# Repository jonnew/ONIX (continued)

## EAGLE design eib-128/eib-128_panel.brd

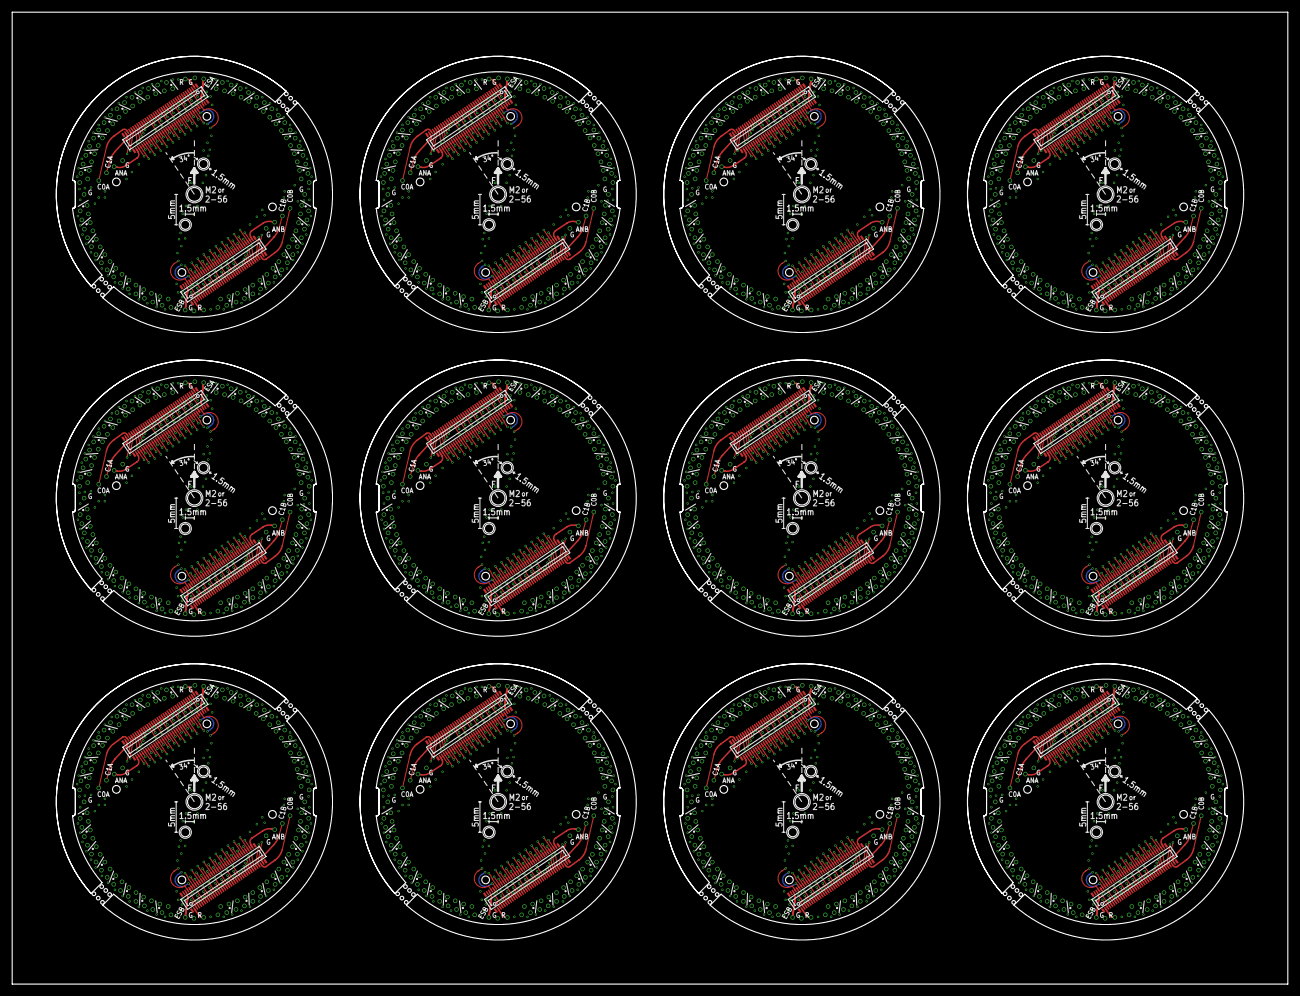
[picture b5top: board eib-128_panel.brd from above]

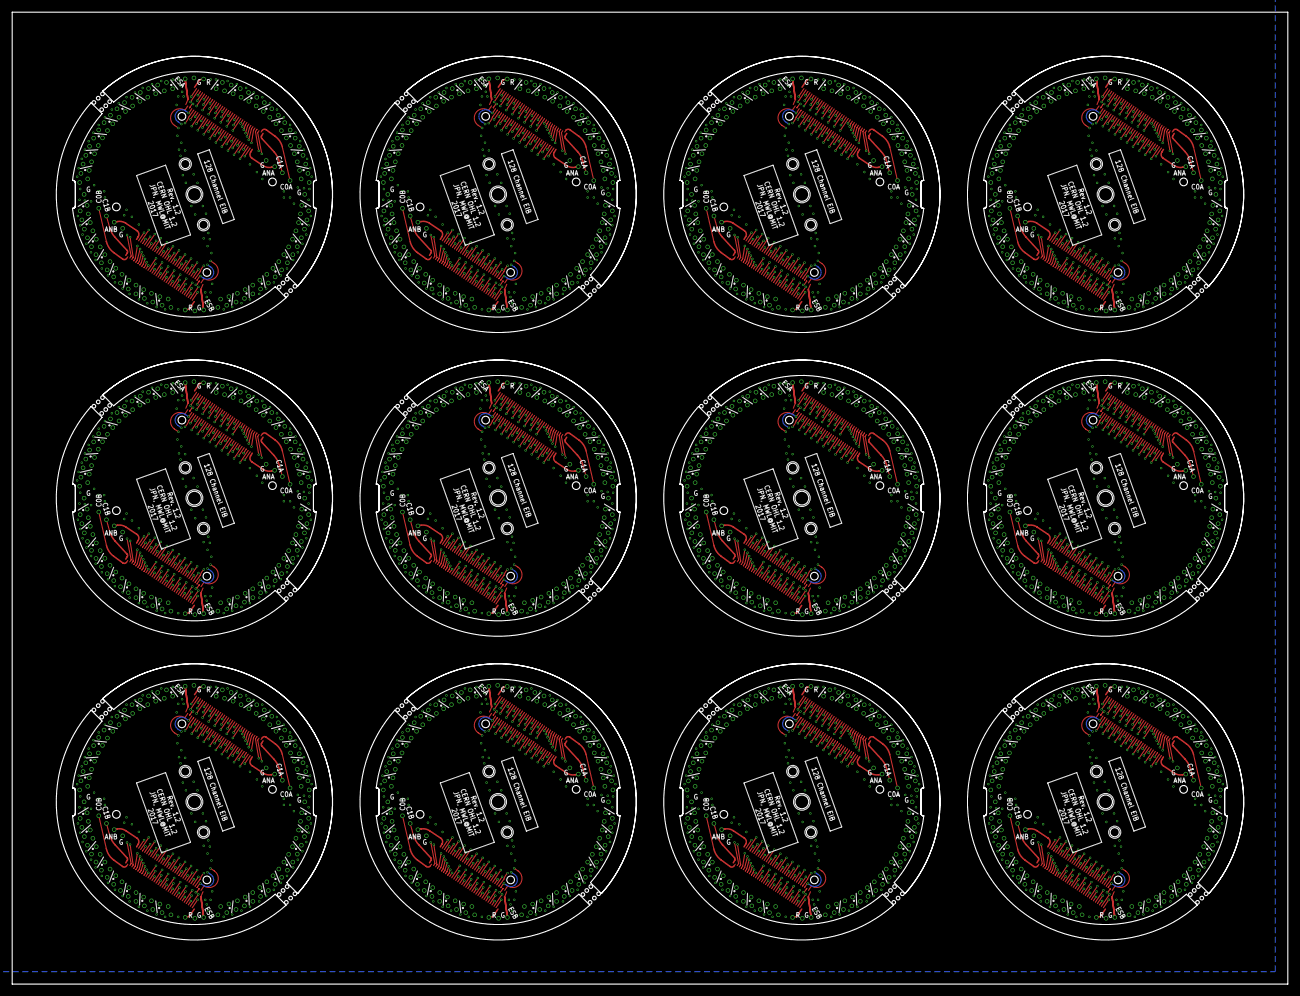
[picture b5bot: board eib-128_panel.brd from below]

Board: 4 copper layers, 210.0 x 160.0 mm, 612 parts (192 on the bottom side), 1657 nets.

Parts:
A, A1, A2, A3, A4, A5, A6, A7, A8, A9, A10, A11: DF40HEAD; DF40-70HEAD
AN_A, AN_A1, AN_A2, AN_A3, AN_A4, AN_A5, AN_A6, AN_A7, AN_A8, AN_A9, AN_A10, AN_A11: LRG_GP; GOLDPIN_0.5ID_0.7OD
AN_B, AN_B1, AN_B2, AN_B3, AN_B4, AN_B5, AN_B6, AN_B7, AN_B8, AN_B9, AN_B10, AN_B11: LRG_GP; GOLDPIN_0.5ID_0.7OD
B, B1, B2, B3, B4, B5, B6, B7, B8, B9, B10, B11: DF40HEAD; DF40-70HEAD
CAT0_A, CAT0_A1, CAT0_A2, CAT0_A3, CAT0_A4, CAT0_A5, CAT0_A6, CAT0_A7, CAT0_A8, CAT0_A9, CAT0_A10, CAT0_A11, CAT0_B, CAT0_B1, CAT0_B2, CAT0_B3, CAT0_B4, CAT0_B5, CAT0_B6, CAT0_B7, CAT0_B8, CAT0_B9, CAT0_B10, CAT0_B11, CAT1_A, CAT1_A1, CAT1_A2, CAT1_A3, CAT1_A4, CAT1_A5, CAT1_A6, CAT1_A7, CAT1_A8, CAT1_A9, CAT1_A10, CAT1_A11, CAT1_B, CAT1_B1, CAT1_B2, CAT1_B3, CAT1_B4, CAT1_B5, CAT1_B6, CAT1_B7, CAT1_B8, CAT1_B9, CAT1_B10, CAT1_B11: LRG_GP; GOLDPIN_0.5ID_0.7OD
ESTIM_A, ESTIM_A1, ESTIM_A2, ESTIM_A3, ESTIM_A4, ESTIM_A5, ESTIM_A6, ESTIM_A7, ESTIM_A8, ESTIM_A9, ESTIM_A10, ESTIM_A11: LRG_GP; GOLDPIN_0.5ID_0.7OD
ESTIM_B, ESTIM_B1, ESTIM_B2, ESTIM_B3, ESTIM_B4, ESTIM_B5, ESTIM_B6, ESTIM_B7, ESTIM_B8, ESTIM_B9, ESTIM_B10, ESTIM_B11: LRG_GP; GOLDPIN_0.5ID_0.7OD
GND0, GND1, GND2, GND3, GND4, GND5, GND6, GND7, GND8, GND9, GND10, GND11, GND12, GND13, GND14, GND15, GND16, GND17, GND18, GND19, GND20, GND21, GND22, GND23, GND24, GND25, GND26, GND27, GND28, GND29, GND30, GND31, GND32, GND33, GND34, GND35, GND36, GND37, GND38, GND39, GND40, GND41, GND42, GND43, GND44, GND45, GND46, GND47: LRG_GP; GOLDPIN_0.5ID_0.7OD
REF_A0, REF_A1, REF_A2, REF_A3, REF_A4, REF_A5, REF_A6, REF_A7, REF_A8, REF_A9, REF_A10, REF_A11: LRG_GP; GOLDPIN_0.5ID_0.7OD
REF_B0, REF_B1, REF_B2, REF_B3, REF_B4, REF_B5, REF_B6, REF_B7, REF_B8, REF_B9, REF_B10, REF_B11: LRG_GP; GOLDPIN_0.5ID_0.7OD
SHLD_A, SHLD_A1, SHLD_A2, SHLD_A3, SHLD_A4, SHLD_A5, SHLD_A6, SHLD_A7, SHLD_A8, SHLD_A9, SHLD_A10, SHLD_A11: LRG_GP; GOLDPIN_0.5ID_0.7OD
SHLD_B, SHLD_B1, SHLD_B2, SHLD_B3, SHLD_B4, SHLD_B5, SHLD_B6, SHLD_B7, SHLD_B8, SHLD_B9, SHLD_B10, SHLD_B11: LRG_GP; GOLDPIN_0.5ID_0.7OD
TET0, TET32, TET64, TET96, TET128, TET160, TET192, TET224, TET256, TET288, TET320, TET352: 0; TETRODE_128_0.5ID_0.7OD
TET1, TET33, TET65, TET97, TET129, TET161, TET193, TET225, TET257, TET289, TET321, TET353: 1; TETRODE_128_0.5ID_0.7OD
TET2, TET34, TET66, TET98, TET130, TET162, TET194, TET226, TET258, TET290, TET322, TET354: 2; TETRODE_128_0.5ID_0.7OD
TET3, TET35, TET67, TET99, TET131, TET163, TET195, TET227, TET259, TET291, TET323, TET355: 3; TETRODE_128_0.5ID_0.7OD
TET4, TET36, TET68, TET100, TET132, TET164, TET196, TET228, TET260, TET292, TET324, TET356: 4; TETRODE_128_0.5ID_0.7OD
TET5, TET37, TET69, TET101, TET133, TET165, TET197, TET229, TET261, TET293, TET325, TET357: 5; TETRODE_128_0.5ID_0.7OD
TET6, TET38, TET70, TET102, TET134, TET166, TET198, TET230, TET262, TET294, TET326, TET358: 6; TETRODE_128_0.5ID_0.7OD
TET7, TET39, TET71, TET103, TET135, TET167, TET199, TET231, TET263, TET295, TET327, TET359: 7; TETRODE_128_0.5ID_0.7OD
TET8, TET40, TET72, TET104, TET136, TET168, TET200, TET232, TET264, TET296, TET328, TET360: 8; TETRODE_128_0.5ID_0.7OD
TET9, TET41, TET73, TET105, TET137, TET169, TET201, TET233, TET265, TET297, TET329, TET361: 9; TETRODE_128_0.5ID_0.7OD
TET10, TET42, TET74, TET106, TET138, TET170, TET202, TET234, TET266, TET298, TET330, TET362: 10; TETRODE_128_0.5ID_0.7OD
TET11, TET43, TET75, TET107, TET139, TET171, TET203, TET235, TET267, TET299, TET331, TET363: 11; TETRODE_128_0.5ID_0.7OD
TET12, TET44, TET76, TET108, TET140, TET172, TET204, TET236, TET268, TET300, TET332, TET364: 12; TETRODE_128_0.5ID_0.7OD
TET13, TET45, TET77, TET109, TET141, TET173, TET205, TET237, TET269, TET301, TET333, TET365: 13; TETRODE_128_0.5ID_0.7OD
TET14, TET46, TET78, TET110, TET142, TET174, TET206, TET238, TET270, TET302, TET334, TET366: 14; TETRODE_128_0.5ID_0.7OD
TET15, TET47, TET79, TET111, TET143, TET175, TET207, TET239, TET271, TET303, TET335, TET367: 15; TETRODE_128_0.5ID_0.7OD
TET16, TET48, TET80, TET112, TET144, TET176, TET208, TET240, TET272, TET304, TET336, TET368: 16; TETRODE_128_0.5ID_0.7OD
TET17, TET49, TET81, TET113, TET145, TET177, TET209, TET241, TET273, TET305, TET337, TET369: 17; TETRODE_128_0.5ID_0.7OD
TET18, TET50, TET82, TET114, TET146, TET178, TET210, TET242, TET274, TET306, TET338, TET370: 18; TETRODE_128_0.5ID_0.7OD
TET19, TET51, TET83, TET115, TET147, TET179, TET211, TET243, TET275, TET307, TET339, TET371: 19; TETRODE_128_0.5ID_0.7OD
TET20, TET52, TET84, TET116, TET148, TET180, TET212, TET244, TET276, TET308, TET340, TET372: 20; TETRODE_128_0.5ID_0.7OD
TET21, TET53, TET85, TET117, TET149, TET181, TET213, TET245, TET277, TET309, TET341, TET373: 21; TETRODE_128_0.5ID_0.7OD
TET22, TET54, TET86, TET118, TET150, TET182, TET214, TET246, TET278, TET310, TET342, TET374: 22; TETRODE_128_0.5ID_0.7OD
TET23, TET55, TET87, TET119, TET151, TET183, TET215, TET247, TET279, TET311, TET343, TET375: 23; TETRODE_128_0.5ID_0.7OD
TET24, TET56, TET88, TET120, TET152, TET184, TET216, TET248, TET280, TET312, TET344, TET376: 24; TETRODE_128_0.5ID_0.7OD
TET25, TET57, TET89, TET121, TET153, TET185, TET217, TET249, TET281, TET313, TET345, TET377: 25; TETRODE_128_0.5ID_0.7OD
TET26, TET58, TET90, TET122, TET154, TET186, TET218, TET250, TET282, TET314, TET346, TET378: 26; TETRODE_128_0.5ID_0.7OD
TET27, TET59, TET91, TET123, TET155, TET187, TET219, TET251, TET283, TET315, TET347, TET379: 27; TETRODE_128_0.5ID_0.7OD
TET28, TET60, TET92, TET124, TET156, TET188, TET220, TET252, TET284, TET316, TET348, TET380: 28; TETRODE_128_0.5ID_0.7OD
TET29, TET61, TET93, TET125, TET157, TET189, TET221, TET253, TET285, TET317, TET349, TET381: 29; TETRODE_128_0.5ID_0.7OD
TET30, TET62, TET94, TET126, TET158, TET190, TET222, TET254, TET286, TET318, TET350, TET382: 30; TETRODE_128_0.5ID_0.7OD
TET31, TET63, TET95, TET127, TET159, TET191, TET223, TET255, TET287, TET319, TET351, TET383: 31; TETRODE_128_0.5ID_0.7OD
U$1, U$2, U$3, U$4, U$5, U$6, U$7, U$8, U$9, U$10, U$11, U$12: EIB_MOUNT_A

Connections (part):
AN_A: A.36, AN_A.P$1
AN_A1: A1.36, AN_A1.P$1
AN_A2: A2.36, AN_A2.P$1
AN_A3: A3.36, AN_A3.P$1
AN_A4: A4.36, AN_A4.P$1
AN_A5: A5.36, AN_A5.P$1
AN_A6: A6.36, AN_A6.P$1
AN_A7: A7.36, AN_A7.P$1
AN_A8: A8.36, AN_A8.P$1
AN_A9: A9.36, AN_A9.P$1
AN_A10: A10.36, AN_A10.P$1
AN_A11: A11.36, AN_A11.P$1
AN_B: AN_B.P$1, B.36
AN_B1: AN_B1.P$1, B1.36
AN_B2: AN_B2.P$1, B2.36
AN_B3: AN_B3.P$1, B3.36
AN_B4: AN_B4.P$1, B4.36
AN_B5: AN_B5.P$1, B5.36
AN_B6: AN_B6.P$1, B6.36
AN_B7: AN_B7.P$1, B7.36
AN_B8: AN_B8.P$1, B8.36
AN_B9: AN_B9.P$1, B9.36
AN_B10: AN_B10.P$1, B10.36
AN_B11: AN_B11.P$1, B11.36
CAT0_A: A.34, CAT0_A.P$1
CAT0_A1: A1.34, CAT0_A1.P$1
CAT0_A2: A2.34, CAT0_A2.P$1
CAT0_A3: A3.34, CAT0_A3.P$1
CAT0_A4: A4.34, CAT0_A4.P$1
CAT0_A5: A5.34, CAT0_A5.P$1
CAT0_A6: A6.34, CAT0_A6.P$1
CAT0_A7: A7.34, CAT0_A7.P$1
CAT0_A8: A8.34, CAT0_A8.P$1
CAT0_A9: A9.34, CAT0_A9.P$1
CAT0_A10: A10.34, CAT0_A10.P$1
CAT0_A11: A11.34, CAT0_A11.P$1
CAT0_B: B.34, CAT0_B.P$1
CAT0_B1: B1.34, CAT0_B1.P$1
CAT0_B2: B2.34, CAT0_B2.P$1
CAT0_B3: B3.34, CAT0_B3.P$1
CAT0_B4: B4.34, CAT0_B4.P$1
CAT0_B5: B5.34, CAT0_B5.P$1
CAT0_B6: B6.34, CAT0_B6.P$1
CAT0_B7: B7.34, CAT0_B7.P$1
CAT0_B8: B8.34, CAT0_B8.P$1
CAT0_B9: B9.34, CAT0_B9.P$1
CAT0_B10: B10.34, CAT0_B10.P$1
CAT0_B11: B11.34, CAT0_B11.P$1
CAT1_A: A.35, CAT1_A.P$1
CAT1_A1: A1.35, CAT1_A1.P$1
CAT1_A2: A2.35, CAT1_A2.P$1
CAT1_A3: A3.35, CAT1_A3.P$1
CAT1_A4: A4.35, CAT1_A4.P$1
CAT1_A5: A5.35, CAT1_A5.P$1
CAT1_A6: A6.35, CAT1_A6.P$1
CAT1_A7: A7.35, CAT1_A7.P$1
CAT1_A8: A8.35, CAT1_A8.P$1
CAT1_A9: A9.35, CAT1_A9.P$1
CAT1_A10: A10.35, CAT1_A10.P$1
CAT1_A11: A11.35, CAT1_A11.P$1
CAT1_B: B.35, CAT1_B.P$1
CAT1_B1: B1.35, CAT1_B1.P$1
CAT1_B2: B2.35, CAT1_B2.P$1
CAT1_B3: B3.35, CAT1_B3.P$1
CAT1_B4: B4.35, CAT1_B4.P$1
CAT1_B5: B5.35, CAT1_B5.P$1
CAT1_B6: B6.35, CAT1_B6.P$1
CAT1_B7: B7.35, CAT1_B7.P$1
CAT1_B8: B8.35, CAT1_B8.P$1
CAT1_B9: B9.35, CAT1_B9.P$1
CAT1_B10: B10.35, CAT1_B10.P$1
CAT1_B11: B11.35, CAT1_B11.P$1
ESTIM_A: A.69, ESTIM_A.P$1
ESTIM_A1: A1.69, ESTIM_A1.P$1
ESTIM_A2: A2.69, ESTIM_A2.P$1
ESTIM_A3: A3.69, ESTIM_A3.P$1
ESTIM_A4: A4.69, ESTIM_A4.P$1
ESTIM_A5: A5.69, ESTIM_A5.P$1
ESTIM_A6: A6.69, ESTIM_A6.P$1
ESTIM_A7: A7.69, ESTIM_A7.P$1
ESTIM_A8: A8.69, ESTIM_A8.P$1
ESTIM_A9: A9.69, ESTIM_A9.P$1
ESTIM_A10: A10.69, ESTIM_A10.P$1
ESTIM_A11: A11.69, ESTIM_A11.P$1
ESTIM_B: B.69, ESTIM_B.P$1
ESTIM_B1: B1.69, ESTIM_B1.P$1
ESTIM_B2: B2.69, ESTIM_B2.P$1
ESTIM_B3: B3.69, ESTIM_B3.P$1
ESTIM_B4: B4.69, ESTIM_B4.P$1
ESTIM_B5: B5.69, ESTIM_B5.P$1
ESTIM_B6: B6.69, ESTIM_B6.P$1
ESTIM_B7: B7.69, ESTIM_B7.P$1
ESTIM_B8: B8.69, ESTIM_B8.P$1
ESTIM_B9: B9.69, ESTIM_B9.P$1
ESTIM_B10: B10.69, ESTIM_B10.P$1
ESTIM_B11: B11.69, ESTIM_B11.P$1
GND: A.70, A.M1, A.M2, A.M3, A.M4, A1.70, A1.M1, A1.M2, A1.M3, A1.M4, A2.70, A2.M1, A2.M2, A2.M3, A2.M4, A3.70, A3.M1, A3.M2, A3.M3, A3.M4, A4.70, A4.M1, A4.M2, A4.M3, A4.M4, A5.70, A5.M1, A5.M2, A5.M3, A5.M4, A6.70, A6.M1, A6.M2, A6.M3, A6.M4, A7.70, A7.M1, A7.M2, A7.M3, A7.M4, A8.70, A8.M1, A8.M2, A8.M3, A8.M4, A9.70, A9.M1, A9.M2, A9.M3, A9.M4, A10.70, A10.M1, A10.M2, A10.M3, A10.M4, A11.70, A11.M1, A11.M2, A11.M3, A11.M4, B.70, B.M1, B.M2, B.M3, B.M4, B1.70, B1.M1, B1.M2, B1.M3, B1.M4, B2.70, B2.M1, B2.M2, B2.M3, B2.M4, B3.70, B3.M1, B3.M2, B3.M3, B3.M4, B4.70, B4.M1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
unnamed: A1.33, TET39.3
unnamed: A1.32, TET39.2
unnamed: A1.31, TET39.1
unnamed: A1.30, TET39.0
unnamed: A1.29, TET38.3
unnamed: A1.28, TET38.2
unnamed: A1.27, TET38.1
unnamed: A1.26, TET38.0
unnamed: A1.25, TET37.3
unnamed: A1.24, TET37.2
unnamed: A1.23, TET37.1
unnamed: A1.22, TET37.0
unnamed: A1.21, TET36.3
unnamed: A1.20, TET36.2
unnamed: A1.19, TET36.1
unnamed: A1.18, TET36.0
unnamed: A1.17, TET35.3
unnamed: A1.16, TET35.2
unnamed: A1.15, TET35.1
unnamed: A1.14, TET35.0
unnamed: A1.13, TET34.3
unnamed: A1.12, TET34.2
unnamed: A1.11, TET34.1
unnamed: A1.10, TET34.0
unnamed: A1.9, TET33.3
unnamed: A1.8, TET33.2
unnamed: A1.7, TET33.1
unnamed: A1.6, TET33.0
unnamed: A1.5, TET32.3
unnamed: A1.4, TET32.2
unnamed: A1.3, TET32.1
unnamed: A1.38, TET40.1
unnamed: A1.39, TET40.2
unnamed: A1.40, TET40.3
unnamed: A1.41, TET41.0
unnamed: A1.42, TET41.1
unnamed: A1.43, TET41.2
unnamed: A1.44, TET41.3
unnamed: A1.45, TET42.0
unnamed: A1.46, TET42.1
unnamed: A1.47, TET42.2
unnamed: A1.48, TET42.3
unnamed: A1.49, TET43.0
unnamed: A1.50, TET43.1
unnamed: A1.51, TET43.2
unnamed: A1.52, TET43.3
unnamed: A1.53, TET44.0
unnamed: A1.54, TET44.1
unnamed: A1.55, TET44.2
unnamed: A1.56, TET44.3
unnamed: A1.57, TET45.0
unnamed: A1.58, TET45.1
unnamed: A1.59, TET45.2
unnamed: A1.60, TET45.3
unnamed: A1.61, TET46.0
unnamed: A1.62, TET46.1
unnamed: A1.63, TET46.2
unnamed: A1.64, TET46.3
unnamed: A1.65, TET47.0
unnamed: A1.66, TET47.1
unnamed: A1.67, TET47.2
unnamed: A1.68, TET47.3
unnamed: A1.2, TET32.0
unnamed: A1.37, TET40.0
unnamed: B.33, TET23.0
unnamed: B.32, TET23.1
unnamed: B.31, TET23.2
unnamed: B.30, TET23.3
unnamed: B.29, TET22.0
unnamed: B.28, TET22.1
unnamed: B.27, TET22.2
unnamed: B.26, TET22.3
unnamed: B.25, TET21.0
unnamed: B.24, TET21.1
unnamed: B.23, TET21.2
unnamed: B.22, TET21.3
unnamed: B.21, TET20.0
unnamed: B.20, TET20.1
unnamed: B.19, TET20.2
unnamed: B.18, TET20.3
unnamed: B.17, TET19.0
unnamed: B.16, TET19.1
unnamed: B.15, TET19.2
unnamed: B.14, TET19.3
unnamed: B.13, TET18.0
unnamed: B.12, TET18.1
unnamed: B.11, TET18.2
unnamed: B.10, TET18.3
unnamed: B.9, TET17.0
unnamed: B.8, TET17.1
unnamed: B.7, TET17.2
unnamed: B.6, TET17.3
unnamed: B.5, TET16.0
unnamed: B.4, TET16.1
unnamed: B.3, TET16.2
unnamed: B.38, TET24.2
unnamed: B.39, TET24.1
unnamed: B.40, TET24.0
unnamed: B.41, TET25.3
unnamed: B.42, TET25.2
unnamed: B.43, TET25.1
unnamed: B.44, TET25.0
unnamed: B.45, TET26.3
unnamed: B.46, TET26.2
unnamed: B.47, TET26.1
unnamed: B.48, TET26.0
unnamed: B.49, TET27.3
unnamed: B.50, TET27.2
unnamed: B.51, TET27.1
unnamed: B.52, TET27.0
unnamed: B.53, TET28.3
unnamed: B.54, TET28.2
unnamed: B.55, TET28.1
unnamed: B.56, TET28.0
unnamed: B.57, TET29.3
unnamed: B.58, TET29.2
unnamed: B.59, TET29.1
unnamed: B.60, TET29.0
unnamed: B.61, TET30.3
unnamed: B.62, TET30.2
unnamed: B.63, TET30.1
unnamed: B.64, TET30.0
unnamed: B.65, TET31.3
unnamed: B.66, TET31.2
unnamed: B.67, TET31.1
unnamed: B.68, TET31.0
unnamed: B.2, TET16.3
unnamed: B.37, TET24.3
unnamed: B1.33, TET55.0
unnamed: B1.32, TET55.1
unnamed: B1.31, TET55.2
unnamed: B1.30, TET55.3
unnamed: B1.29, TET54.0
unnamed: B1.28, TET54.1
unnamed: B1.27, TET54.2
unnamed: B1.26, TET54.3
unnamed: B1.25, TET53.0
unnamed: B1.24, TET53.1
unnamed: B1.23, TET53.2
unnamed: B1.22, TET53.3
unnamed: B1.21, TET52.0
unnamed: B1.20, TET52.1
unnamed: B1.19, TET52.2
unnamed: B1.18, TET52.3
unnamed: B1.17, TET51.0
unnamed: B1.16, TET51.1
unnamed: B1.15, TET51.2
unnamed: B1.14, TET51.3
unnamed: B1.13, TET50.0
unnamed: B1.12, TET50.1
unnamed: B1.11, TET50.2
unnamed: B1.10, TET50.3
unnamed: B1.9, TET49.0
unnamed: B1.8, TET49.1
unnamed: B1.7, TET49.2
unnamed: B1.6, TET49.3
unnamed: B1.5, TET48.0
unnamed: B1.4, TET48.1
unnamed: B1.3, TET48.2
unnamed: B1.38, TET56.2
unnamed: B1.39, TET56.1
unnamed: B1.40, TET56.0
unnamed: B1.41, TET57.3
unnamed: B1.42, TET57.2
unnamed: B1.43, TET57.1
unnamed: B1.44, TET57.0
unnamed: B1.45, TET58.3
unnamed: B1.46, TET58.2
unnamed: B1.47, TET58.1
unnamed: B1.48, TET58.0
unnamed: B1.49, TET59.3
unnamed: B1.50, TET59.2
unnamed: B1.51, TET59.1
unnamed: B1.52, TET59.0
unnamed: B1.53, TET60.3
unnamed: B1.54, TET60.2
unnamed: B1.55, TET60.1
unnamed: B1.56, TET60.0
unnamed: B1.57, TET61.3
unnamed: B1.58, TET61.2
unnamed: B1.59, TET61.1
unnamed: B1.60, TET61.0
unnamed: B1.61, TET62.3
unnamed: B1.62, TET62.2
unnamed: B1.63, TET62.1
unnamed: B1.64, TET62.0
unnamed: B1.65, TET63.3
unnamed: B1.66, TET63.2
unnamed: B1.67, TET63.1
unnamed: B1.68, TET63.0
unnamed: B1.2, TET48.3
unnamed: B1.37, TET56.3
unnamed: A2.33, TET71.3
unnamed: A2.32, TET71.2
unnamed: A2.31, TET71.1
unnamed: A2.30, TET71.0
unnamed: A2.29, TET70.3
unnamed: A2.28, TET70.2
unnamed: A.33, TET7.3
unnamed: A.32, TET7.2
unnamed: A.31, TET7.1
unnamed: A.30, TET7.0
unnamed: A.29, TET6.3
unnamed: A.28, TET6.2
unnamed: A.27, TET6.1
unnamed: A.26, TET6.0
unnamed: A.25, TET5.3
unnamed: A.24, TET5.2
unnamed: A.23, TET5.1
unnamed: A.22, TET5.0
unnamed: A.21, TET4.3
unnamed: A.20, TET4.2
unnamed: A.19, TET4.1
unnamed: A.18, TET4.0
unnamed: A.17, TET3.3
unnamed: A.16, TET3.2
unnamed: A.15, TET3.1
unnamed: A.14, TET3.0
unnamed: A.13, TET2.3
unnamed: A.12, TET2.2
unnamed: A.11, TET2.1
unnamed: A.10, TET2.0
unnamed: A.9, TET1.3
unnamed: A.8, TET1.2
unnamed: A.7, TET1.1
unnamed: A.6, TET1.0
unnamed: A.5, TET0.3
unnamed: A.4, TET0.2
unnamed: A.3, TET0.1
unnamed: A.2, TET0.0
unnamed: A.38, TET8.1
unnamed: A.39, TET8.2
unnamed: A.40, TET8.3
unnamed: A.41, TET9.0
unnamed: A.42, TET9.1
unnamed: A.43, TET9.2
unnamed: A.44, TET9.3
unnamed: A.45, TET10.0
unnamed: A.46, TET10.1
unnamed: A.47, TET10.2
unnamed: A.48, TET10.3
unnamed: A.49, TET11.0
unnamed: A.50, TET11.1
unnamed: A.51, TET11.2
unnamed: A.52, TET11.3
unnamed: A.53, TET12.0
unnamed: A.54, TET12.1
unnamed: A.55, TET12.2
unnamed: A.56, TET12.3
unnamed: A.57, TET13.0
unnamed: A.58, TET13.1
unnamed: A.59, TET13.2
unnamed: A.60, TET13.3
unnamed: A.61, TET14.0
unnamed: A.62, TET14.1
unnamed: A.63, TET14.2
unnamed: A.64, TET14.3
unnamed: A.65, TET15.0
unnamed: A.66, TET15.1
unnamed: A.67, TET15.2
unnamed: A.68, TET15.3
unnamed: A2.27, TET70.1
unnamed: A2.26, TET70.0
unnamed: A2.25, TET69.3
unnamed: A2.24, TET69.2
unnamed: A2.23, TET69.1
unnamed: A2.22, TET69.0
unnamed: A2.21, TET68.3
unnamed: A2.20, TET68.2
unnamed: A2.19, TET68.1
unnamed: A2.18, TET68.0
unnamed: A2.17, TET67.3
unnamed: A2.16, TET67.2
unnamed: A2.15, TET67.1
unnamed: A2.14, TET67.0
unnamed: A2.13, TET66.3
unnamed: A2.12, TET66.2
unnamed: A2.11, TET66.1
unnamed: A2.10, TET66.0
unnamed: A2.9, TET65.3
unnamed: A2.8, TET65.2
unnamed: A2.7, TET65.1
unnamed: A2.6, TET65.0
unnamed: A2.5, TET64.3
unnamed: A2.4, TET64.2
unnamed: A2.3, TET64.1
unnamed: A2.38, TET72.1
unnamed: A2.39, TET72.2
unnamed: A2.40, TET72.3
unnamed: A2.41, TET73.0
unnamed: A2.42, TET73.1
unnamed: A2.43, TET73.2
unnamed: A2.44, TET73.3
unnamed: A2.45, TET74.0
unnamed: A2.46, TET74.1
unnamed: A2.47, TET74.2
unnamed: A2.48, TET74.3
unnamed: A2.49, TET75.0
unnamed: A2.50, TET75.1
unnamed: A2.51, TET75.2
unnamed: A2.52, TET75.3
unnamed: A2.53, TET76.0
unnamed: A2.54, TET76.1
unnamed: A2.55, TET76.2
unnamed: A2.56, TET76.3
unnamed: A2.57, TET77.0
unnamed: A2.58, TET77.1
unnamed: A2.59, TET77.2
unnamed: A2.60, TET77.3
unnamed: A2.61, TET78.0
unnamed: A2.62, TET78.1
unnamed: A2.63, TET78.2
unnamed: A2.64, TET78.3
unnamed: A2.65, TET79.0
unnamed: A2.66, TET79.1
unnamed: A2.67, TET79.2
unnamed: A2.68, TET79.3
unnamed: A2.2, TET64.0
unnamed: A2.37, TET72.0
unnamed: B2.33, TET87.0
unnamed: B2.32, TET87.1
unnamed: B2.31, TET87.2
unnamed: B2.30, TET87.3
unnamed: B2.29, TET86.0
unnamed: B2.28, TET86.1
unnamed: B2.27, TET86.2
unnamed: B2.26, TET86.3
unnamed: B2.25, TET85.0
unnamed: B2.24, TET85.1
unnamed: B2.23, TET85.2
unnamed: B2.22, TET85.3
unnamed: B2.21, TET84.0
unnamed: B2.20, TET84.1
unnamed: B2.19, TET84.2
unnamed: B2.18, TET84.3
unnamed: B2.17, TET83.0
unnamed: B2.16, TET83.1
unnamed: B2.15, TET83.2
unnamed: B2.14, TET83.3
unnamed: B2.13, TET82.0
unnamed: B2.12, TET82.1
unnamed: B2.11, TET82.2
unnamed: B2.10, TET82.3
unnamed: B2.9, TET81.0
unnamed: B2.8, TET81.1
unnamed: B2.7, TET81.2
unnamed: B2.6, TET81.3
unnamed: B2.5, TET80.0
unnamed: B2.4, TET80.1
unnamed: B2.3, TET80.2
unnamed: B2.38, TET88.2
unnamed: B2.39, TET88.1
unnamed: B2.40, TET88.0
unnamed: B2.41, TET89.3
unnamed: B2.42, TET89.2
unnamed: B2.43, TET89.1
unnamed: B2.44, TET89.0
unnamed: B2.45, TET90.3
unnamed: B2.46, TET90.2
unnamed: B2.47, TET90.1
unnamed: B2.48, TET90.0
unnamed: B2.49, TET91.3
unnamed: B2.50, TET91.2
unnamed: B2.51, TET91.1
unnamed: B2.52, TET91.0
unnamed: B2.53, TET92.3
unnamed: B2.54, TET92.2
unnamed: B2.55, TET92.1
unnamed: B2.56, TET92.0
unnamed: B2.57, TET93.3
unnamed: B2.58, TET93.2
unnamed: B2.59, TET93.1
unnamed: B2.60, TET93.0
unnamed: B2.61, TET94.3
unnamed: B2.62, TET94.2
unnamed: B2.63, TET94.1
unnamed: B2.64, TET94.0
unnamed: B2.65, TET95.3
unnamed: B2.66, TET95.2
unnamed: B2.67, TET95.1
unnamed: B2.68, TET95.0
unnamed: B2.2, TET80.3
unnamed: B2.37, TET88.3
unnamed: A3.33, TET103.3
unnamed: A3.32, TET103.2
unnamed: A3.31, TET103.1
unnamed: A3.30, TET103.0
unnamed: A3.29, TET102.3
unnamed: A3.28, TET102.2
unnamed: A3.27, TET102.1
unnamed: A3.26, TET102.0
unnamed: A3.25, TET101.3
unnamed: A3.24, TET101.2
unnamed: A3.23, TET101.1
unnamed: A3.22, TET101.0
unnamed: A3.21, TET100.3
unnamed: A3.20, TET100.2
unnamed: A3.19, TET100.1
unnamed: A3.18, TET100.0
unnamed: A3.17, TET99.3
unnamed: A3.16, TET99.2
unnamed: A3.15, TET99.1
unnamed: A3.14, TET99.0
unnamed: A3.13, TET98.3
unnamed: A3.12, TET98.2
unnamed: A3.11, TET98.1
unnamed: A3.10, TET98.0
unnamed: A3.9, TET97.3
unnamed: A3.8, TET97.2
unnamed: A3.7, TET97.1
unnamed: A3.6, TET97.0
unnamed: A3.5, TET96.3
unnamed: A3.4, TET96.2
unnamed: A3.3, TET96.1
unnamed: A3.38, TET104.1
unnamed: A3.39, TET104.2
unnamed: A3.40, TET104.3
unnamed: A3.41, TET105.0
unnamed: A3.42, TET105.1
unnamed: A3.43, TET105.2
unnamed: A3.44, TET105.3
unnamed: A3.45, TET106.0
unnamed: A3.46, TET106.1
unnamed: A3.47, TET106.2
unnamed: A3.48, TET106.3
unnamed: A3.49, TET107.0
unnamed: A3.50, TET107.1
unnamed: A3.51, TET107.2
unnamed: A3.52, TET107.3
unnamed: A3.53, TET108.0
unnamed: A3.54, TET108.1
unnamed: A3.55, TET108.2
unnamed: A3.56, TET108.3
unnamed: A3.57, TET109.0
unnamed: A3.58, TET109.1
unnamed: A3.59, TET109.2
unnamed: A3.60, TET109.3
unnamed: A3.61, TET110.0
unnamed: A3.62, TET110.1
unnamed: A3.63, TET110.2
unnamed: A3.64, TET110.3
unnamed: A3.65, TET111.0
unnamed: A3.66, TET111.1
unnamed: A3.67, TET111.2
unnamed: A3.68, TET111.3
unnamed: A3.2, TET96.0
unnamed: A3.37, TET104.0
unnamed: B3.33, TET119.0
unnamed: B3.32, TET119.1
unnamed: B3.31, TET119.2
unnamed: B3.30, TET119.3
unnamed: B3.29, TET118.0
unnamed: B3.28, TET118.1
unnamed: B3.27, TET118.2
unnamed: B3.26, TET118.3
unnamed: B3.25, TET117.0
unnamed: B3.24, TET117.1
unnamed: B3.23, TET117.2
unnamed: B3.22, TET117.3
unnamed: B3.21, TET116.0
unnamed: B3.20, TET116.1
unnamed: B3.19, TET116.2
unnamed: B3.18, TET116.3
unnamed: B3.17, TET115.0
unnamed: B3.16, TET115.1
unnamed: B3.15, TET115.2
unnamed: B3.14, TET115.3
unnamed: B3.13, TET114.0
unnamed: B3.12, TET114.1
unnamed: B3.11, TET114.2
unnamed: B3.10, TET114.3
unnamed: B3.9, TET113.0
unnamed: B3.8, TET113.1
unnamed: B3.7, TET113.2
unnamed: B3.6, TET113.3
unnamed: B3.5, TET112.0
unnamed: B3.4, TET112.1
unnamed: B3.3, TET112.2
unnamed: B3.38, TET120.2
unnamed: B3.39, TET120.1
unnamed: B3.40, TET120.0
unnamed: B3.41, TET121.3
unnamed: B3.42, TET121.2
unnamed: B3.43, TET121.1
unnamed: B3.44, TET121.0
unnamed: B3.45, TET122.3
unnamed: B3.46, TET122.2
unnamed: B3.47, TET122.1
unnamed: B3.48, TET122.0
unnamed: B3.49, TET123.3
unnamed: B3.50, TET123.2
unnamed: B3.51, TET123.1
unnamed: B3.52, TET123.0
unnamed: B3.53, TET124.3
unnamed: B3.54, TET124.2
unnamed: B3.55, TET124.1
unnamed: B3.56, TET124.0
unnamed: B3.57, TET125.3
unnamed: B3.58, TET125.2
unnamed: B3.59, TET125.1
unnamed: B3.60, TET125.0
unnamed: B3.61, TET126.3
unnamed: B3.62, TET126.2
unnamed: B3.63, TET126.1
unnamed: B3.64, TET126.0
unnamed: B3.65, TET127.3
unnamed: B3.66, TET127.2
unnamed: B3.67, TET127.1
unnamed: B3.68, TET127.0
unnamed: B3.2, TET112.3
unnamed: B3.37, TET120.3
unnamed: A4.33, TET135.3
unnamed: A4.32, TET135.2
unnamed: A4.31, TET135.1
unnamed: A4.30, TET135.0
unnamed: A4.29, TET134.3
unnamed: A4.28, TET134.2
unnamed: A4.27, TET134.1
unnamed: A4.26, TET134.0
unnamed: A4.25, TET133.3
unnamed: A4.24, TET133.2
unnamed: A4.23, TET133.1
unnamed: A4.22, TET133.0
unnamed: A4.21, TET132.3
unnamed: A4.20, TET132.2
unnamed: A4.19, TET132.1
unnamed: A4.18, TET132.0
unnamed: A4.17, TET131.3
unnamed: A4.16, TET131.2
unnamed: A4.15, TET131.1
unnamed: A4.14, TET131.0
unnamed: A4.13, TET130.3
unnamed: A4.12, TET130.2
unnamed: A4.11, TET130.1
unnamed: A4.10, TET130.0
unnamed: A4.9, TET129.3
unnamed: A4.8, TET129.2
unnamed: A4.7, TET129.1
unnamed: A4.6, TET129.0
unnamed: A4.5, TET128.3
unnamed: A4.4, TET128.2
unnamed: A4.3, TET128.1
unnamed: A4.38, TET136.1
unnamed: A4.39, TET136.2
unnamed: A4.40, TET136.3
unnamed: A4.41, TET137.0
unnamed: A4.42, TET137.1
unnamed: A4.43, TET137.2
unnamed: A4.44, TET137.3
unnamed: A4.45, TET138.0
unnamed: A4.46, TET138.1
unnamed: A4.47, TET138.2
unnamed: A4.48, TET138.3
unnamed: A4.49, TET139.0
unnamed: A4.50, TET139.1
unnamed: A4.51, TET139.2
unnamed: A4.52, TET139.3
unnamed: A4.53, TET140.0
unnamed: A4.54, TET140.1
unnamed: A4.55, TET140.2
unnamed: A4.56, TET140.3
unnamed: A4.57, TET141.0
unnamed: A4.58, TET141.1
unnamed: A4.59, TET141.2
unnamed: A4.60, TET141.3
unnamed: A4.61, TET142.0
unnamed: A4.62, TET142.1
unnamed: A4.63, TET142.2
unnamed: A4.64, TET142.3
unnamed: A4.65, TET143.0
unnamed: A4.66, TET143.1
unnamed: A4.67, TET143.2
unnamed: A4.68, TET143.3
unnamed: A4.2, TET128.0
unnamed: A4.37, TET136.0
unnamed: B4.33, TET151.0
unnamed: B4.32, TET151.1
unnamed: B4.31, TET151.2
unnamed: B4.30, TET151.3
unnamed: B4.29, TET150.0
unnamed: B4.28, TET150.1
unnamed: B4.27, TET150.2
unnamed: B4.26, TET150.3
unnamed: B4.25, TET149.0
unnamed: B4.24, TET149.1
unnamed: B4.23, TET149.2
unnamed: B4.22, TET149.3
unnamed: B4.21, TET148.0
unnamed: B4.20, TET148.1
unnamed: B4.19, TET148.2
unnamed: B4.18, TET148.3
unnamed: B4.17, TET147.0
unnamed: B4.16, TET147.1
unnamed: B4.15, TET147.2
unnamed: B4.14, TET147.3
unnamed: B4.13, TET146.0
unnamed: B4.12, TET146.1
unnamed: B4.11, TET146.2
unnamed: B4.10, TET146.3
unnamed: B4.9, TET145.0
unnamed: B4.8, TET145.1
unnamed: B4.7, TET145.2
unnamed: B4.6, TET145.3
unnamed: B4.5, TET144.0
unnamed: B4.4, TET144.1
unnamed: B4.3, TET144.2
unnamed: B4.38, TET152.2
unnamed: B4.39, TET152.1
unnamed: B4.40, TET152.0
unnamed: B4.41, TET153.3
unnamed: B4.42, TET153.2
unnamed: B4.43, TET153.1
unnamed: B4.44, TET153.0
unnamed: B4.45, TET154.3
unnamed: B4.46, TET154.2
unnamed: B4.47, TET154.1
unnamed: B4.48, TET154.0
unnamed: B4.49, TET155.3
unnamed: B4.50, TET155.2
unnamed: B4.51, TET155.1
unnamed: B4.52, TET155.0
unnamed: B4.53, TET156.3
unnamed: B4.54, TET156.2
unnamed: B4.55, TET156.1
unnamed: B4.56, TET156.0
unnamed: B4.57, TET157.3
unnamed: B4.58, TET157.2
unnamed: B4.59, TET157.1
unnamed: B4.60, TET157.0
unnamed: B4.61, TET158.3
unnamed: B4.62, TET158.2
unnamed: B4.63, TET158.1
unnamed: B4.64, TET158.0
unnamed: B4.65, TET159.3
unnamed: B4.66, TET159.2
unnamed: B4.67, TET159.1
unnamed: B4.68, TET159.0
unnamed: B4.2, TET144.3
unnamed: B4.37, TET152.3
unnamed: A5.33, TET167.3
unnamed: A5.32, TET167.2
unnamed: A5.31, TET167.1
unnamed: A5.30, TET167.0
unnamed: A5.29, TET166.3
unnamed: A5.28, TET166.2
unnamed: A5.27, TET166.1
unnamed: A5.26, TET166.0
unnamed: A5.25, TET165.3
unnamed: A5.24, TET165.2
unnamed: A5.23, TET165.1
unnamed: A5.22, TET165.0
unnamed: A5.21, TET164.3
unnamed: A5.20, TET164.2
unnamed: A5.19, TET164.1
unnamed: A5.18, TET164.0
unnamed: A5.17, TET163.3
unnamed: A5.16, TET163.2
unnamed: A5.15, TET163.1
unnamed: A5.14, TET163.0
unnamed: A5.13, TET162.3
unnamed: A5.12, TET162.2
unnamed: A5.11, TET162.1
unnamed: A5.10, TET162.0
unnamed: A5.9, TET161.3
unnamed: A5.8, TET161.2
unnamed: A5.7, TET161.1
unnamed: A5.6, TET161.0
unnamed: A5.5, TET160.3
unnamed: A5.4, TET160.2
unnamed: A5.3, TET160.1
unnamed: A5.38, TET168.1
unnamed: A5.39, TET168.2
unnamed: A5.40, TET168.3
unnamed: A5.41, TET169.0
unnamed: A5.42, TET169.1
unnamed: A5.43, TET169.2
unnamed: A5.44, TET169.3
unnamed: A5.45, TET170.0
unnamed: A5.46, TET170.1
unnamed: A5.47, TET170.2
unnamed: A5.48, TET170.3
unnamed: A5.49, TET171.0
unnamed: A5.50, TET171.1
unnamed: A5.51, TET171.2
unnamed: A5.52, TET171.3
unnamed: A5.53, TET172.0
unnamed: A5.54, TET172.1
unnamed: A5.55, TET172.2
unnamed: A5.56, TET172.3
unnamed: A5.57, TET173.0
unnamed: A5.58, TET173.1
unnamed: A5.59, TET173.2
unnamed: A5.60, TET173.3
unnamed: A5.61, TET174.0
unnamed: A5.62, TET174.1
unnamed: A5.63, TET174.2
unnamed: A5.64, TET174.3
unnamed: A5.65, TET175.0
unnamed: A5.66, TET175.1
unnamed: A5.67, TET175.2
unnamed: A5.68, TET175.3
unnamed: A5.2, TET160.0
unnamed: A5.37, TET168.0
unnamed: B5.33, TET183.0
unnamed: B5.32, TET183.1
unnamed: B5.31, TET183.2
unnamed: B5.30, TET183.3
unnamed: B5.29, TET182.0
unnamed: B5.28, TET182.1
unnamed: B5.27, TET182.2
unnamed: B5.26, TET182.3
unnamed: B5.25, TET181.0
unnamed: B5.24, TET181.1
unnamed: B5.23, TET181.2
unnamed: B5.22, TET181.3
unnamed: B5.21, TET180.0
unnamed: B5.20, TET180.1
unnamed: B5.19, TET180.2
unnamed: B5.18, TET180.3
unnamed: B5.17, TET179.0
unnamed: B5.16, TET179.1
unnamed: B5.15, TET179.2
unnamed: B5.14, TET179.3
unnamed: B5.13, TET178.0
unnamed: B5.12, TET178.1
unnamed: B5.11, TET178.2
unnamed: B5.10, TET178.3
unnamed: B5.9, TET177.0
unnamed: B5.8, TET177.1
unnamed: B5.7, TET177.2
unnamed: B5.6, TET177.3
unnamed: B5.5, TET176.0
unnamed: B5.4, TET176.1
unnamed: B5.3, TET176.2
unnamed: B5.38, TET184.2
unnamed: B5.39, TET184.1
unnamed: B5.40, TET184.0
unnamed: B5.41, TET185.3
unnamed: B5.42, TET185.2
unnamed: B5.43, TET185.1
unnamed: B5.44, TET185.0
unnamed: B5.45, TET186.3
unnamed: B5.46, TET186.2
unnamed: B5.47, TET186.1
unnamed: B5.48, TET186.0
unnamed: B5.49, TET187.3
unnamed: B5.50, TET187.2
unnamed: B5.51, TET187.1
unnamed: B5.52, TET187.0
unnamed: B5.53, TET188.3
unnamed: B5.54, TET188.2
unnamed: B5.55, TET188.1
unnamed: B5.56, TET188.0
unnamed: B5.57, TET189.3
unnamed: B5.58, TET189.2
unnamed: B5.59, TET189.1
unnamed: B5.60, TET189.0
unnamed: B5.61, TET190.3
unnamed: B5.62, TET190.2
unnamed: B5.63, TET190.1
unnamed: B5.64, TET190.0
unnamed: B5.65, TET191.3
unnamed: B5.66, TET191.2
unnamed: B5.67, TET191.1
unnamed: B5.68, TET191.0
unnamed: B5.2, TET176.3
unnamed: B5.37, TET184.3
unnamed: A6.33, TET199.3
unnamed: A6.32, TET199.2
unnamed: A6.31, TET199.1
unnamed: A6.30, TET199.0
unnamed: A6.29, TET198.3
unnamed: A6.28, TET198.2
unnamed: A6.27, TET198.1
unnamed: A6.26, TET198.0
unnamed: A6.25, TET197.3
unnamed: A6.24, TET197.2
unnamed: A6.23, TET197.1
unnamed: A6.22, TET197.0
unnamed: A6.21, TET196.3
unnamed: A6.20, TET196.2
unnamed: A6.19, TET196.1
unnamed: A6.18, TET196.0
unnamed: A6.17, TET195.3
unnamed: A6.16, TET195.2
unnamed: A6.15, TET195.1
unnamed: A6.14, TET195.0
unnamed: A6.13, TET194.3
unnamed: A6.12, TET194.2
unnamed: A6.11, TET194.1
unnamed: A6.10, TET194.0
unnamed: A6.9, TET193.3
unnamed: A6.8, TET193.2
unnamed: A6.7, TET193.1
unnamed: A6.6, TET193.0
unnamed: A6.5, TET192.3
unnamed: A6.4, TET192.2
unnamed: A6.3, TET192.1
unnamed: A6.38, TET200.1
unnamed: A6.39, TET200.2
unnamed: A6.40, TET200.3
unnamed: A6.41, TET201.0
unnamed: A6.42, TET201.1
unnamed: A6.43, TET201.2
unnamed: A6.44, TET201.3
unnamed: A6.45, TET202.0
unnamed: A6.46, TET202.1
unnamed: A6.47, TET202.2
unnamed: A6.48, TET202.3
unnamed: A6.49, TET203.0
unnamed: A6.50, TET203.1
unnamed: A6.51, TET203.2
unnamed: A6.52, TET203.3
unnamed: A6.53, TET204.0
unnamed: A6.54, TET204.1
unnamed: A6.55, TET204.2
unnamed: A6.56, TET204.3
unnamed: A6.57, TET205.0
unnamed: A6.58, TET205.1
unnamed: A6.59, TET205.2
unnamed: A6.60, TET205.3
unnamed: A6.61, TET206.0
unnamed: A6.62, TET206.1
unnamed: A6.63, TET206.2
unnamed: A6.64, TET206.3
unnamed: A6.65, TET207.0
unnamed: A6.66, TET207.1
unnamed: A6.67, TET207.2
unnamed: A6.68, TET207.3
unnamed: A6.2, TET192.0
unnamed: A6.37, TET200.0
unnamed: B6.33, TET215.0
unnamed: B6.32, TET215.1
unnamed: B6.31, TET215.2
unnamed: B6.30, TET215.3
unnamed: B6.29, TET214.0
unnamed: B6.28, TET214.1
unnamed: B6.27, TET214.2
unnamed: B6.26, TET214.3
unnamed: B6.25, TET213.0
unnamed: B6.24, TET213.1
unnamed: B6.23, TET213.2
unnamed: B6.22, TET213.3
unnamed: B6.21, TET212.0
unnamed: B6.20, TET212.1
unnamed: B6.19, TET212.2
unnamed: B6.18, TET212.3
unnamed: B6.17, TET211.0
unnamed: B6.16, TET211.1
unnamed: B6.15, TET211.2
unnamed: B6.14, TET211.3
unnamed: B6.13, TET210.0
unnamed: B6.12, TET210.1
unnamed: B6.11, TET210.2
unnamed: B6.10, TET210.3
unnamed: B6.9, TET209.0
unnamed: B6.8, TET209.1
unnamed: B6.7, TET209.2
unnamed: B6.6, TET209.3
unnamed: B6.5, TET208.0
unnamed: B6.4, TET208.1
unnamed: B6.3, TET208.2
unnamed: B6.38, TET216.2
unnamed: B6.39, TET216.1
unnamed: B6.40, TET216.0
unnamed: B6.41, TET217.3
unnamed: B6.42, TET217.2
unnamed: B6.43, TET217.1
unnamed: B6.44, TET217.0
unnamed: B6.45, TET218.3
unnamed: B6.46, TET218.2
unnamed: B6.47, TET218.1
unnamed: B6.48, TET218.0
unnamed: B6.49, TET219.3
unnamed: B6.50, TET219.2
unnamed: B6.51, TET219.1
unnamed: B6.52, TET219.0
unnamed: B6.53, TET220.3
unnamed: B6.54, TET220.2
unnamed: B6.55, TET220.1
unnamed: B6.56, TET220.0
unnamed: B6.57, TET221.3
unnamed: B6.58, TET221.2
unnamed: B6.59, TET221.1
unnamed: B6.60, TET221.0
unnamed: B6.61, TET222.3
unnamed: B6.62, TET222.2
unnamed: B6.63, TET222.1
unnamed: B6.64, TET222.0
unnamed: B6.65, TET223.3
unnamed: B6.66, TET223.2
unnamed: B6.67, TET223.1
unnamed: B6.68, TET223.0
unnamed: B6.2, TET208.3
unnamed: B6.37, TET216.3
unnamed: A7.33, TET231.3
unnamed: A7.32, TET231.2
unnamed: A7.31, TET231.1
unnamed: A7.30, TET231.0
unnamed: A7.29, TET230.3
unnamed: A7.28, TET230.2
unnamed: A7.27, TET230.1
unnamed: A7.26, TET230.0
unnamed: A7.25, TET229.3
unnamed: A7.24, TET229.2
unnamed: A7.23, TET229.1
unnamed: A7.22, TET229.0
unnamed: A7.21, TET228.3
unnamed: A7.20, TET228.2
unnamed: A7.19, TET228.1
unnamed: A7.18, TET228.0
unnamed: A7.17, TET227.3
unnamed: A7.16, TET227.2
unnamed: A7.15, TET227.1
unnamed: A7.14, TET227.0
unnamed: A7.13, TET226.3
unnamed: A7.12, TET226.2
unnamed: A7.11, TET226.1
unnamed: A7.10, TET226.0
unnamed: A7.9, TET225.3
unnamed: A7.8, TET225.2
unnamed: A7.7, TET225.1
unnamed: A7.6, TET225.0
unnamed: A7.5, TET224.3
unnamed: A7.4, TET224.2
unnamed: A7.3, TET224.1
unnamed: A7.38, TET232.1
unnamed: A7.39, TET232.2
unnamed: A7.40, TET232.3
unnamed: A7.41, TET233.0
unnamed: A7.42, TET233.1
unnamed: A7.43, TET233.2
unnamed: A7.44, TET233.3
unnamed: A7.45, TET234.0
unnamed: A7.46, TET234.1
unnamed: A7.47, TET234.2
unnamed: A7.48, TET234.3
unnamed: A7.49, TET235.0
unnamed: A7.50, TET235.1
unnamed: A7.51, TET235.2
unnamed: A7.52, TET235.3
unnamed: A7.53, TET236.0
unnamed: A7.54, TET236.1
unnamed: A7.55, TET236.2
unnamed: A7.56, TET236.3
unnamed: A7.57, TET237.0
unnamed: A7.58, TET237.1
unnamed: A7.59, TET237.2
unnamed: A7.60, TET237.3
unnamed: A7.61, TET238.0
unnamed: A7.62, TET238.1
unnamed: A7.63, TET238.2
unnamed: A7.64, TET238.3
unnamed: A7.65, TET239.0
unnamed: A7.66, TET239.1
unnamed: A7.67, TET239.2
unnamed: A7.68, TET239.3
unnamed: A7.2, TET224.0
unnamed: A7.37, TET232.0
unnamed: B7.33, TET247.0
unnamed: B7.32, TET247.1
unnamed: B7.31, TET247.2
unnamed: B7.30, TET247.3
unnamed: B7.29, TET246.0
unnamed: B7.28, TET246.1
unnamed: B7.27, TET246.2
unnamed: B7.26, TET246.3
unnamed: B7.25, TET245.0
unnamed: B7.24, TET245.1
unnamed: B7.23, TET245.2
unnamed: B7.22, TET245.3
unnamed: B7.21, TET244.0
unnamed: B7.20, TET244.1
unnamed: B7.19, TET244.2
unnamed: B7.18, TET244.3
unnamed: B7.17, TET243.0
unnamed: B7.16, TET243.1
unnamed: B7.15, TET243.2
unnamed: B7.14, TET243.3
unnamed: B7.13, TET242.0
unnamed: B7.12, TET242.1
unnamed: B7.11, TET242.2
unnamed: B7.10, TET242.3
unnamed: B7.9, TET241.0
unnamed: B7.8, TET241.1
unnamed: B7.7, TET241.2
unnamed: B7.6, TET241.3
unnamed: B7.5, TET240.0
unnamed: B7.4, TET240.1
unnamed: B7.3, TET240.2
unnamed: B7.38, TET248.2
unnamed: B7.39, TET248.1
unnamed: B7.40, TET248.0
unnamed: B7.41, TET249.3
unnamed: B7.42, TET249.2
unnamed: B7.43, TET249.1
unnamed: B7.44, TET249.0
unnamed: B7.45, TET250.3
unnamed: B7.46, TET250.2
unnamed: A.37, TET8.0
unnamed: B7.47, TET250.1
unnamed: B7.48, TET250.0
unnamed: B7.49, TET251.3
unnamed: B7.50, TET251.2
unnamed: B7.51, TET251.1
unnamed: B7.52, TET251.0
unnamed: B7.53, TET252.3
unnamed: B7.54, TET252.2
unnamed: B7.55, TET252.1
unnamed: B7.56, TET252.0
unnamed: B7.57, TET253.3
unnamed: B7.58, TET253.2
unnamed: B7.59, TET253.1
unnamed: B7.60, TET253.0
unnamed: B7.61, TET254.3
unnamed: B7.62, TET254.2
unnamed: B7.63, TET254.1
unnamed: B7.64, TET254.0
unnamed: B7.65, TET255.3
unnamed: B7.66, TET255.2
unnamed: B7.67, TET255.1
unnamed: B7.68, TET255.0
unnamed: B7.2, TET240.3
unnamed: B7.37, TET248.3
unnamed: A8.33, TET263.3
unnamed: A8.32, TET263.2
unnamed: A8.31, TET263.1
unnamed: A8.30, TET263.0
unnamed: A8.29, TET262.3
unnamed: A8.28, TET262.2
unnamed: A8.27, TET262.1
unnamed: A8.26, TET262.0
unnamed: A8.25, TET261.3
unnamed: A8.24, TET261.2
unnamed: A8.23, TET261.1
unnamed: A8.22, TET261.0
unnamed: A8.21, TET260.3
unnamed: A8.20, TET260.2
unnamed: A8.19, TET260.1
unnamed: A8.18, TET260.0
unnamed: A8.17, TET259.3
unnamed: A8.16, TET259.2
unnamed: A8.15, TET259.1
unnamed: A8.14, TET259.0
unnamed: A8.13, TET258.3
unnamed: A8.12, TET258.2
unnamed: A8.11, TET258.1
unnamed: A8.10, TET258.0
unnamed: A8.9, TET257.3
unnamed: A8.8, TET257.2
unnamed: A8.7, TET257.1
unnamed: A8.6, TET257.0
unnamed: A8.5, TET256.3
unnamed: A8.4, TET256.2
unnamed: A8.3, TET256.1
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
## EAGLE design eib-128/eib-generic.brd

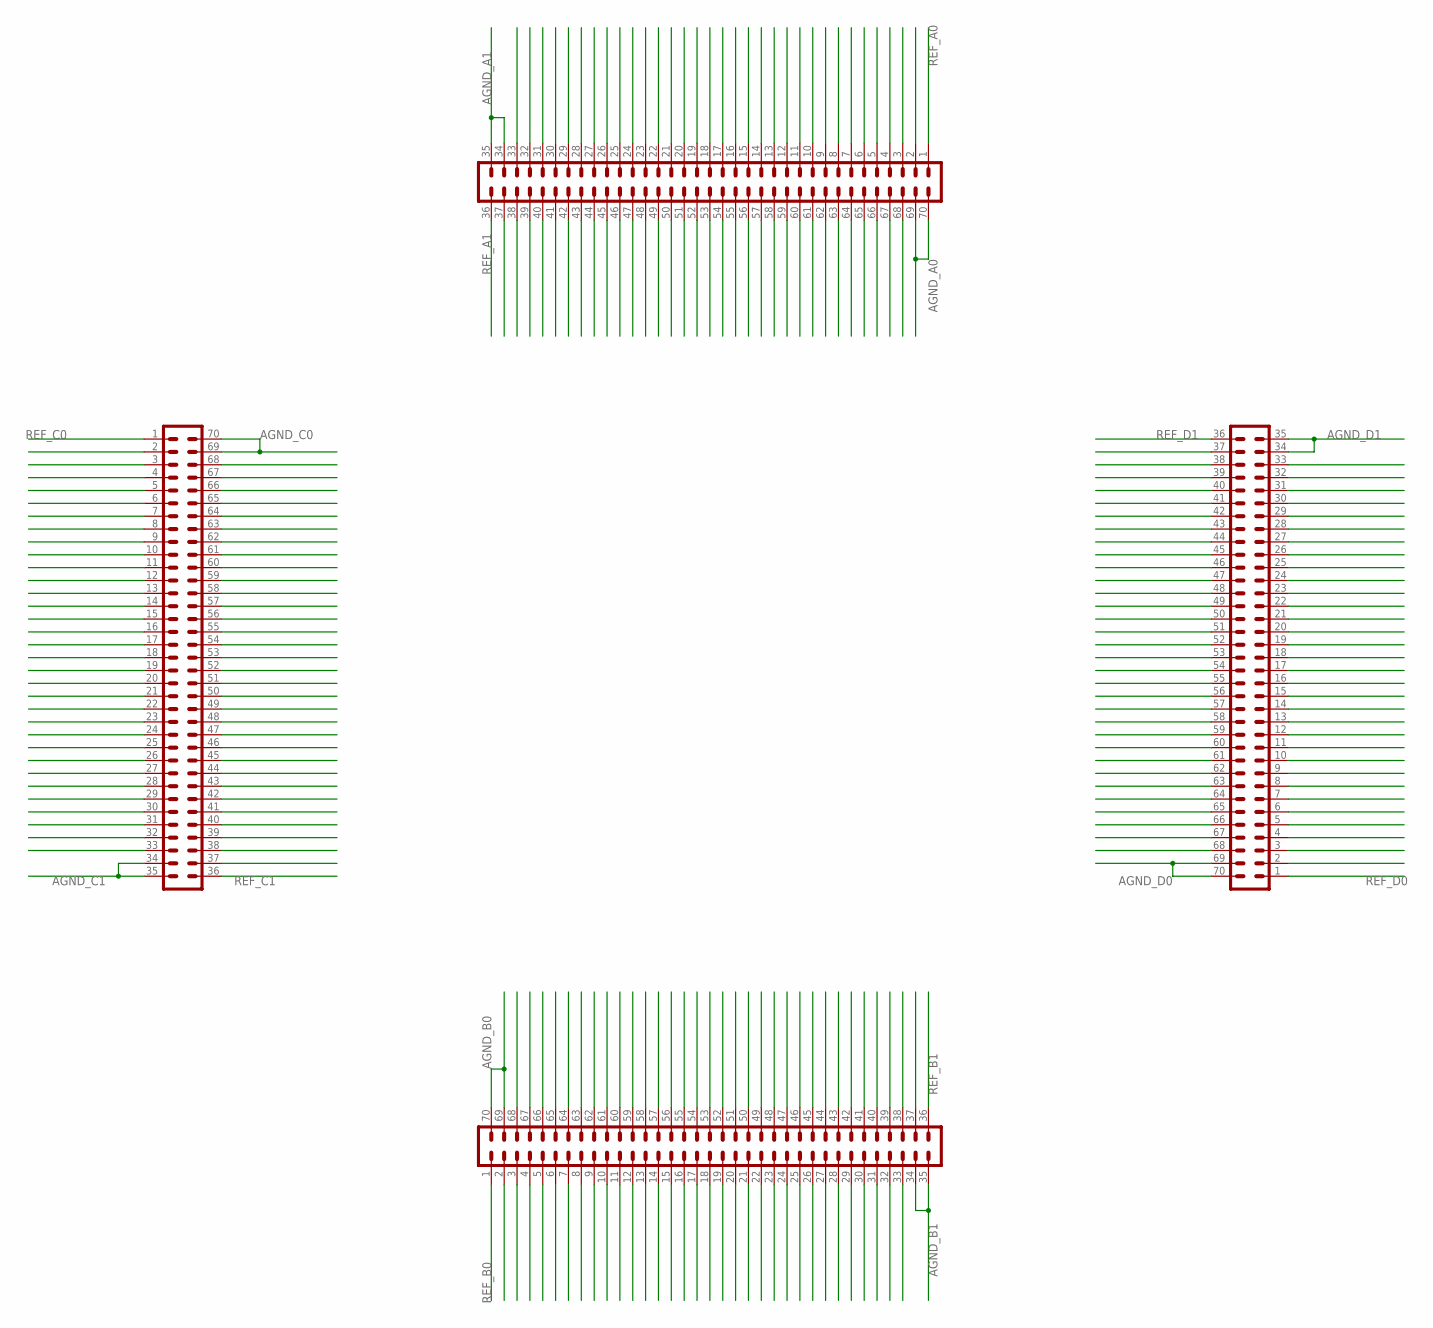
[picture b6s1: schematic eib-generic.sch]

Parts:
A: DF40HEAD; DF40-70HEAD
B: DF40HEAD; DF40-70HEAD
C: DF40HEAD; DF40-70HEAD
D: DF40HEAD; DF40-70HEAD

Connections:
AGND_A0: A.69, A.70
AGND_A1: A.34, A.35
AGND_B0: B.69, B.70
AGND_B1: B.34, B.35
AGND_C0: C.69, C.70
AGND_C1: C.34, C.35
AGND_D0: D.69, D.70
AGND_D1: D.34, D.35
REF_A0: A.1
REF_A1: A.36
REF_B0: B.1
REF_B1: B.36
REF_C0: C.1
REF_C1: C.36
REF_D0: D.1
REF_D1: D.36

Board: 4 copper layers, 4 parts (0 on the bottom side), 8 nets, no tracks yet.
